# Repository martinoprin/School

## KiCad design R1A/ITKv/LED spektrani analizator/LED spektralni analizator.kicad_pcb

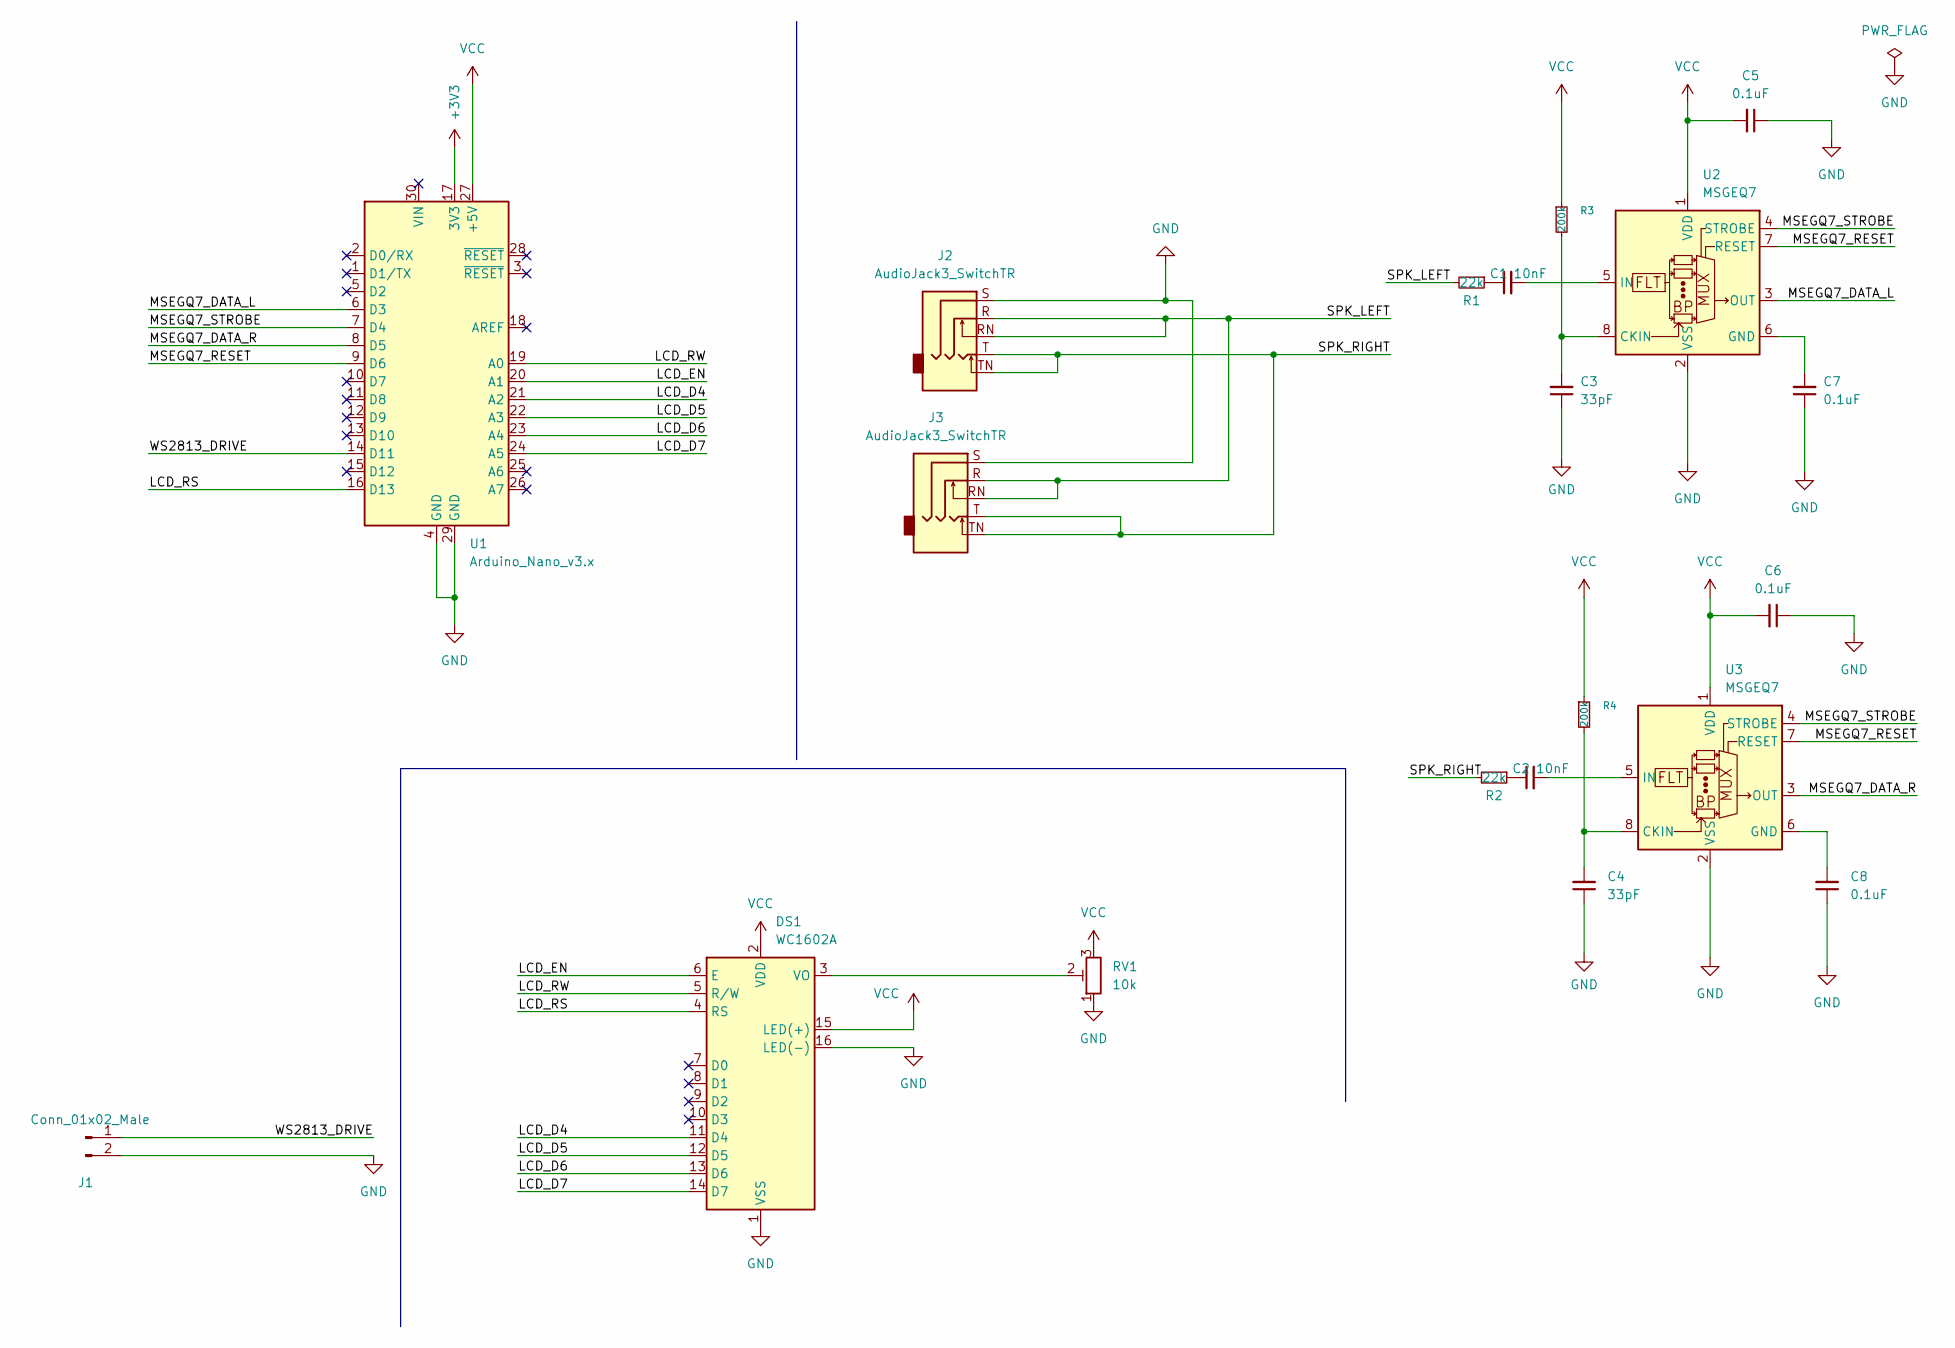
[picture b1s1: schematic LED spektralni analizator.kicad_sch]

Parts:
C1, C2: 10nF; C_Disc_D3.0mm_W2.0mm_P2.50mm
C3, C4: 33pF; C_Disc_D3.0mm_W2.0mm_P2.50mm
C5, C6, C7, C8: 0.1uF; C_Disc_D3.0mm_W2.0mm_P2.50mm
DS1: WC1602A
J1: Conn_01x02_Male; PinHeader_1x02_P2.54mm_Vertical
J2, J3: AudioJack3_SwitchTR; Jack_3.5mm_Ledino_KB3SPRS_Horizontal
R1, R2: 22k; R_Axial_DIN0207_L6.3mm_D2.5mm_P7.62mm_Horizontal
R3, R4: 200k; R_Axial_DIN0207_L6.3mm_D2.5mm_P7.62mm_Horizontal
RV1: 10k; Potentiometer_Piher_PT-6-V_Vertical
U1: Arduino_Nano_v3.x; Arduino_Nano
U2, U3: MSGEQ7; DIP-8_W7.62mm_Socket_LongPads

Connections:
+3V3: U1.17 (3V3)
/LCD_D4: DS1.11 (D4), U1.21 (A2)
/LCD_D5: DS1.12 (D5), U1.22 (A3)
/LCD_D6: DS1.13 (D6), U1.23 (A4)
/LCD_D7: DS1.14 (D7), U1.24 (A5)
/LCD_EN: DS1.6 (E), U1.20 (A1)
/LCD_RS: DS1.4 (RS), U1.16 (D13)
/LCD_RW: DS1.5 (R/W), U1.19 (A0)
/MSEGQ7_DATA_L: U1.6 (D3), U2.3 (OUT)
/MSEGQ7_DATA_R: U1.8 (D5), U3.3 (OUT)
/MSEGQ7_RESET: U1.9 (D6), U2.7 (RESET), U3.7 (RESET)
/MSEGQ7_STROBE: U1.7 (D4), U2.4 (STROBE), U3.4 (STROBE)
/SPK_LEFT: J2.R, J2.RN, J3.R, J3.RN, R1.2
/SPK_RIGHT: J2.T, J2.TN, J3.T, J3.TN, R2.2
/WS2813_DRIVE: J1.1, U1.14 (D11)
GND: C3.1, C4.1, C5.1, C6.1, C7.1, C8.1, DS1.1 (VSS), DS1.16 (LED(-)), J1.2, J2.S, J3.S, RV1.1, U1.4 (GND), U1.29 (GND), U2.2 (VSS), U3.2 (VSS)
unnamed: C1.1, R1.1
unnamed: C1.2, U2.5 (IN)
unnamed: C2.1, R2.1
unnamed: C2.2, U3.5 (IN)
unnamed: C3.2, R3.2, U2.8 (CKIN)
unnamed: C4.2, R4.2, U3.8 (CKIN)
unnamed: C7.2, U2.6 (GND)
unnamed: C8.2, U3.6 (GND)
unnamed: DS1.3 (VO), RV1.2
VCC: C5.2, C6.2, DS1.2 (VDD), DS1.15 (LED(+)), R3.1, R4.1, RV1.3, U1.27 (+5V), U2.1 (VDD), U3.1 (VDD)

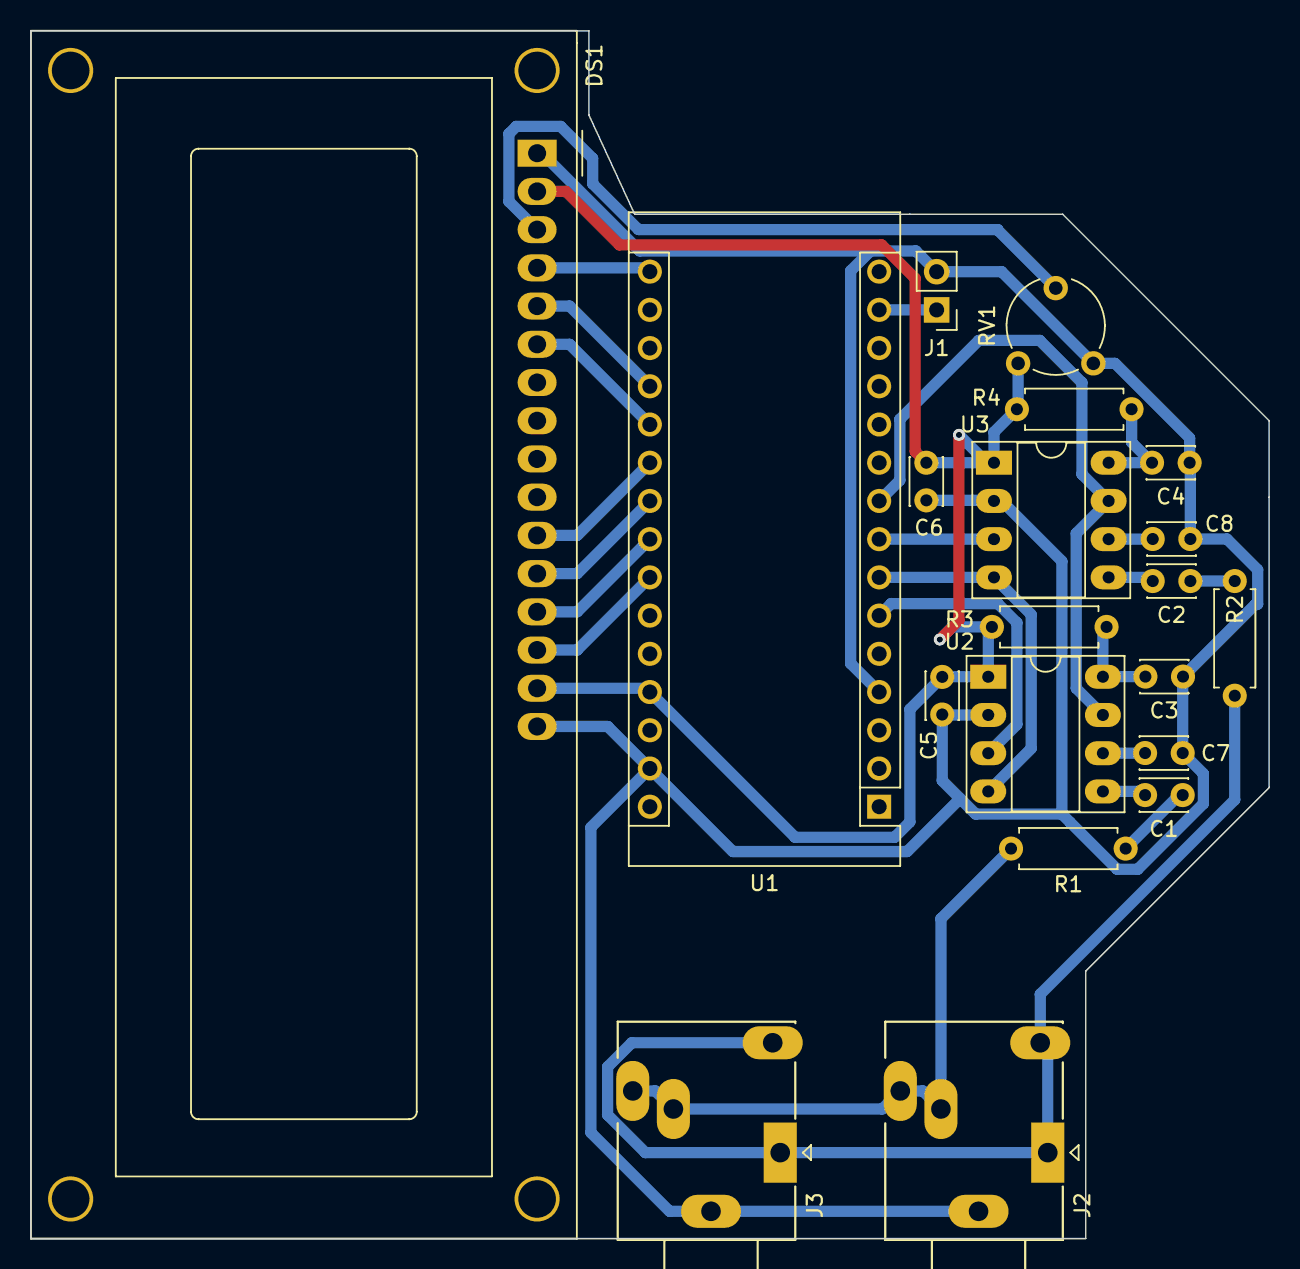
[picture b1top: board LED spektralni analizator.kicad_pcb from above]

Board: 2 copper layers, 82.3 x 80.3 mm, 20 parts (0 on the bottom side), 25 nets.

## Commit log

2024-02-28 .md dodan
2024-02-28 navodial.md
2024-02-28 navodilaa.md
2024-02-28 dodana skola.sql
2024-02-28 update navodil
2024-02-28 nova tabela stranke
2024-02-28 dodana trgovina.sql
2024-02-28 novamapa trgovina
2024-02-28 dodan rpa
2024-02-29 vaje iz datotek
2024-03-11 arduino
2024-04-02 Update Osnovno.md
    samoglasniki
2024-04-03 neki
2024-04-24 Create roles-users
2024-04-24 Update roles-users
2024-04-25 DDL, DML, DCL
2024-04-25 Rename role.md to SQL.md
2024-04-25 Create testB_resitve
2024-04-25 Rename testB_resitve to testB_resitve.md
2024-04-25 konec
2024-05-09 Rename test.md to test-map.md
2024-05-09 Create vpis
2024-05-09 Update vpis
2024-05-09 Rename vpis to vpis.md
2024-05-14 Create TELL-G_P
2024-05-14 Rename TELL-G_P to TELL-G_P.md
2024-05-15 Rename DS3231_Alarms.ino to RVP-Krislej_Integracija.ino
2024-05-21 Ustvarjena Praksa
2024-05-22 web app, terminal app, test
2024-05-22 porocilo 22.5.2024
2024-05-23 update word
2024-05-23 MinimalAPIDEMO
2024-05-27 ip.txt
2024-06-13 praksakoncana
2024-06-13 slova update
2024-06-14 porocilo
2024-10-01 added 4. letnik
2024-10-01 spletne strani
2024-10-01 dodano
2024-11-26 Create INS_UP_DEL
2025-01-07 initial commit from macbook
2025-01-07 vaja11
2025-01-07 forma
2025-01-07 vaja11 prva naloga1
2025-01-07 zdruzevanje datotek
2025-01-10 vaja6 koncana
2025-01-10 vaja7
2025-01-11 update vaj
2025-01-11 vaja5 naloga 3
2025-01-11 vaja 5 4
2025-01-11 vaja5 5
2025-01-11 vaja5 koncana
2025-01-11 vaja7 koncana
2025-01-11 vaja 7 koncana
2025-01-11 naloga 8 v delu
2025-01-11 vaja 8 koncana
2025-01-11 vaja 9 v delu
2025-01-12 9naloga skor
2025-01-12 vaja9 koncana
2025-01-12 vaja10 samo se 4
2025-01-14 vaja10 v dellu
2025-01-14 vaja10koncana
2025-01-14 up to date
2025-01-14 vaja10 -2 koncana
2025-01-14 vaja 11 koncana
2025-01-14 vaja12 3 koncana
2025-01-14 vaja12 - 3.naloga koncana
2025-01-14 vaja12 koncana
2025-01-22 vaja13
2025-01-22 form
2025-01-22 vaja1 konec
2025-01-22 vaja 13.3 v delu
2025-01-22 vaja13.4a konc
2025-01-22 vaja13 koncana
2025-01-28 stile
2025-01-28 narejen edit UI
2025-01-29 vaja13.1init
2025-01-29 vaja14.1konc
2025-02-01 delujoc modal mal bo se treba narest
2025-02-01 neki:
2025-02-02 na novo napisan script treba bo popravt resizing in dokoncat create button
2025-02-05 remove dela ampak color pa positon ne dela pa ne stora se v localstorage pa box
